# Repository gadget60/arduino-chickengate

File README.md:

# arduino-chickengate
Arduino based mechanic door controller

## ...what?
This is a door controller based on an Arduino. It opens a mechanic door of a hen house in the morning and closes it in the evening. That's it, basically. 

## Timing
Current date/time and open/close times are programmable via USB/serial console (need to wake up from power down sleep first by pressing one of the open or close buttons). Due to early sunset in winter time the open/close times are programmable for each month. I use a DS1307 Real Time Clock module, this allows to persist the timetable in its NVRAM.
Available commands:
- `time [hhmm]`: sets the current time
- `date [YYYYMMDD]`: sets the current date
- `gate [MM] [hhmm] [hhmm]`: sets for month MM the open and close times

## Mechanics
The door is openend/closed by a high torque gear motor, driven by a L9110 DC motor driver board. There are two buttons for manual opening/closing the door and two mechanical end switches (top and bottom).

## Power
Main issue is to keep power consumption low, because the controller as well as mechanics are driven by a small solar panel that feeds 4x1.2V rechargeable batteries. First of all, I got rid of the power LED on the ProMicro board by soldering it out. Due to high power consumption of the motor driver board, it is powered off via a transistor when not used. Finally onboard USB is disabled and the ProMicro is set to SLEEP_MODE_PWR_DOWN. Overall this brings power consumption down to around 20uA in idle mode.

## Hardware
- ProMicro Atmega 5V/16MHz (Dev-12640), https://cdn.sparkfun.com/datasheets/Dev/Arduino/Boards/ProMicro16MHzv1.pdf
- DS1307 Real Time Clock module
- L9110 DC motor driver board
- 6V high torque gear motor (ZnDiy-BRY 25GA-6V-80 DC 6V 80rpm)
- Solar panel, 0.5W, max voltage around 9V

## PINS
```
D2  --> I2C data (Realtime clock SDA)
D3  --> I2C clock (Realtime clock SCL)
D7  --> Wake up pin
D6  --> Motor A PWM Speed
D5  --> Motor A Direction
D9  --> Driver Power (Transistor Base)
D14 --> Up button, normally open
D15 --> Down button, normally open
D10 --> End switch top, normally closed
D16 --> End switch bottom, normally closed
```

## Scheme

## Images

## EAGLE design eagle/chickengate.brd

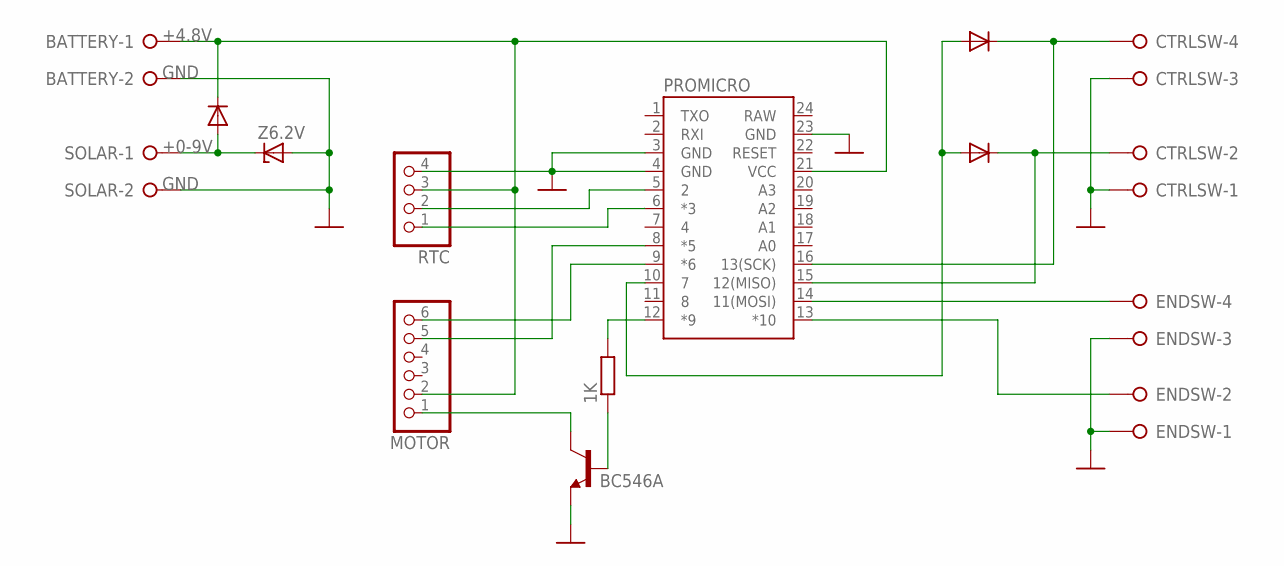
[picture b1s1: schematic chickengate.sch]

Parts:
1K: R-EU_0207/12; 0207/12
BATTERY: W237-02P; W237-132
CTRLSW: W237-04P; W237-4P
D1, D2, D3: 1N4004; DO41-10
ENDSW: W237-04P; W237-4P
MOTOR: PINHD-1X6; 1X06
PROMICRO: SPARKFUN_PRO_MICRO
Q1: BC546A; TO92-EBC
RTC: PINHD-1X4; 1X04
SOLAR: W237-02P; W237-132
Z6.2V: ZPD; DO35Z10

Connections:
+0-9V: D1.A, SOLAR.1, Z6.2V.C
+4.8V: BATTERY.1, D1.C, MOTOR.2, PROMICRO.21 (VCC), RTC.3
GND: BATTERY.2, CTRLSW.1, CTRLSW.3, ENDSW.1, ENDSW.3, PROMICRO.3 (GND), PROMICRO.4 (GND), PROMICRO.23 (GND), Q1.E, RTC.4, SOLAR.2, Z6.2V.A
M1: MOTOR.5, PROMICRO.8 (*5)
M2: MOTOR.6, PROMICRO.9 (*6)
unnamed: 1K.2, PROMICRO.12 (*9)
unnamed: PROMICRO.5 (2), RTC.2
unnamed: PROMICRO.6 (*3), RTC.1
unnamed: 1K.1, Q1.B
unnamed: MOTOR.1, Q1.C
unnamed: CTRLSW.4, D2.C, PROMICRO.16 (13(SCK))
unnamed: CTRLSW.2, D3.C, PROMICRO.15 (12(MISO))
unnamed: D2.A, D3.A, PROMICRO.10 (7)
unnamed: ENDSW.4, PROMICRO.14 (11(MOSI))
unnamed: ENDSW.2, PROMICRO.13 (*10)
RAW: PROMICRO.24 (RAW)

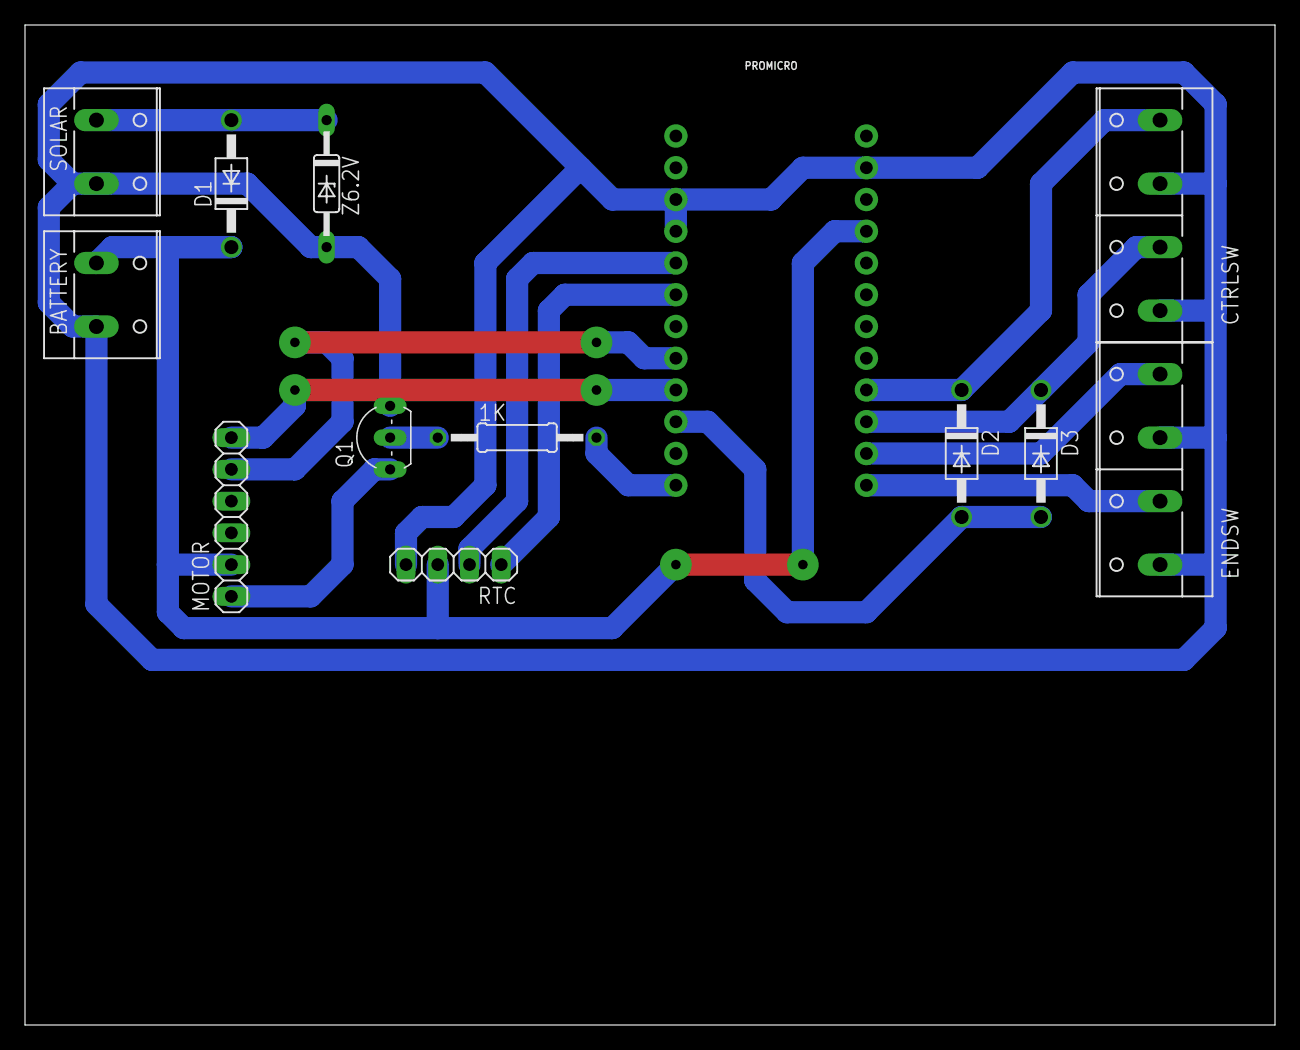
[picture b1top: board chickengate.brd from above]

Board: 2 copper layers, 100.0 x 80.0 mm, 13 parts (0 on the bottom side), 15 nets.

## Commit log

2018-11-28 fix typos
2018-11-28 fix pin description
2018-12-25 add schema
2018-12-25 fix image paths
2018-12-25 fix typo
2018-12-26 update docs
2018-12-26 documentation
2018-12-26 docs

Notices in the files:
parts and their libraries:
SparkFun-Boards: Licensing: Creative Commons ShareAlike 4.0 International - https://creativecommons.org/licenses/by-sa/4.0
